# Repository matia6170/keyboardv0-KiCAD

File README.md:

# Keyboard v0 Design
KiCAD9 Schematic/PCB layout of the first keyboard prototype.

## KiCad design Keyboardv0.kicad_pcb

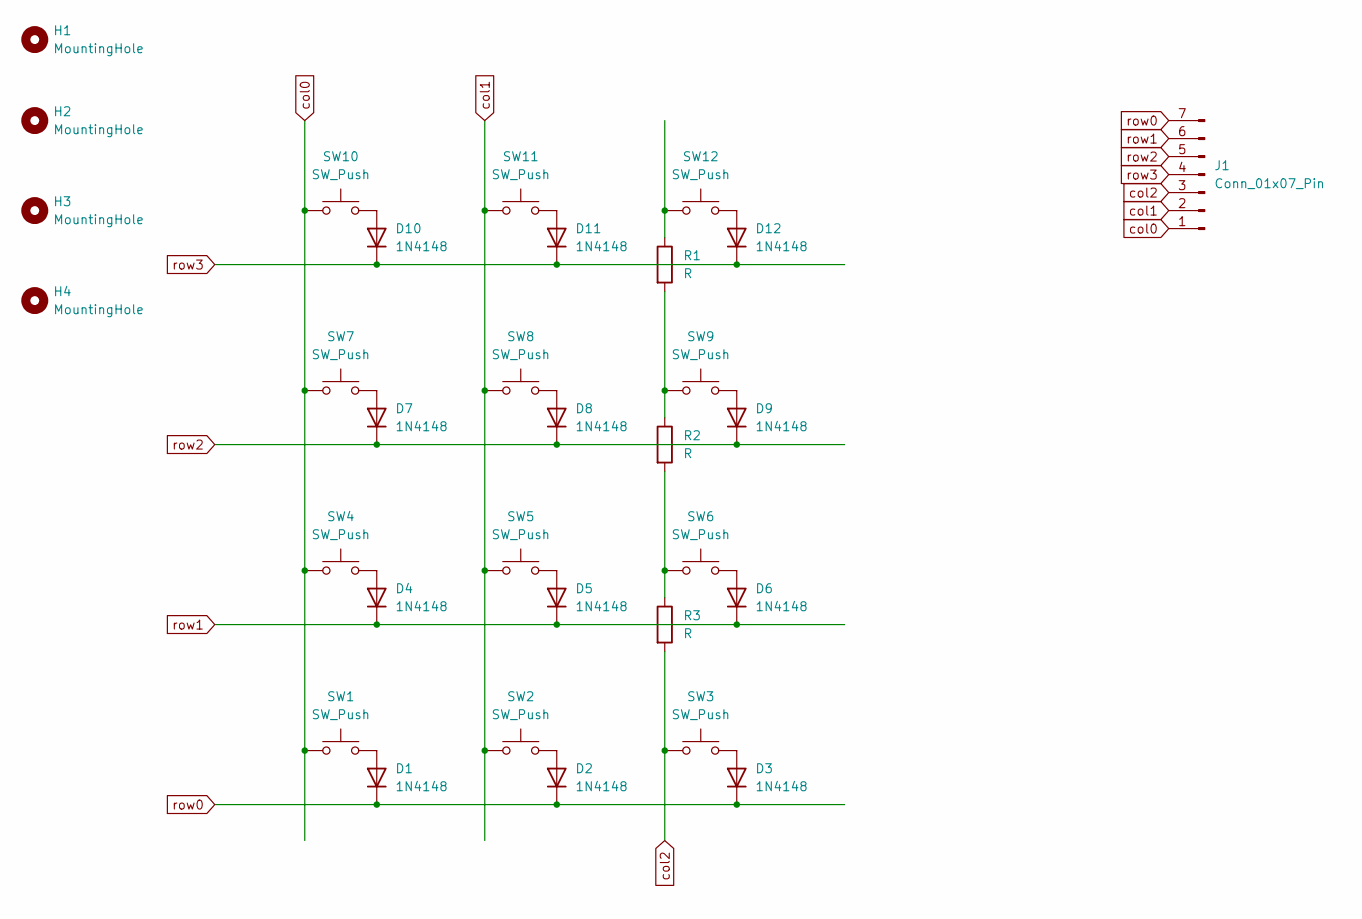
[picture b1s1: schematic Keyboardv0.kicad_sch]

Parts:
D1, D2, D3, D4, D5, D6, D7, D8, D9, D10, D11, D12: 1N4148; D_SOD-123
H1, H2, H3, H4: MountingHole; MountingHole_3.2mm_M3
J1: Conn_01x07_Pin; PinHeader_1x07_P2.54mm_Vertical
R1, R2, R3: R; R_Axial_DIN0204_L3.6mm_D1.6mm_P5.08mm_Horizontal
SW1, SW2, SW3, SW4, SW5, SW6, SW7, SW8, SW9, SW10, SW11, SW12: SW_Push; SW_Cherry_MX_PCB_1.00u

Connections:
unnamed: D1.2 (A), SW1.2
unnamed: D2.2 (A), SW2.2
unnamed: D3.2 (A), SW3.2
unnamed: D4.2 (A), SW4.2
unnamed: D5.2 (A), SW5.2
unnamed: D6.2 (A), SW6.2
unnamed: D7.2 (A), SW7.2
unnamed: D8.2 (A), SW8.2
unnamed: D9.2 (A), SW9.2
unnamed: D10.2 (A), SW10.2
unnamed: D11.2 (A), SW11.2
unnamed: D12.2 (A), SW12.2
unnamed: R1.1, SW12.1
unnamed: R1.2, R2.1, SW9.1
unnamed: R2.2, R3.1, SW6.1
col0: J1.1, SW1.1, SW4.1, SW7.1, SW10.1
col1: J1.2, SW2.1, SW5.1, SW8.1, SW11.1
col2: J1.3, R3.2, SW3.1
row0: D1.1 (K), D2.1 (K), D3.1 (K), J1.7
row1: D4.1 (K), D5.1 (K), D6.1 (K), J1.6
row2: D7.1 (K), D8.1 (K), D9.1 (K), J1.5
row3: D10.1 (K), D11.1 (K), D12.1 (K), J1.4

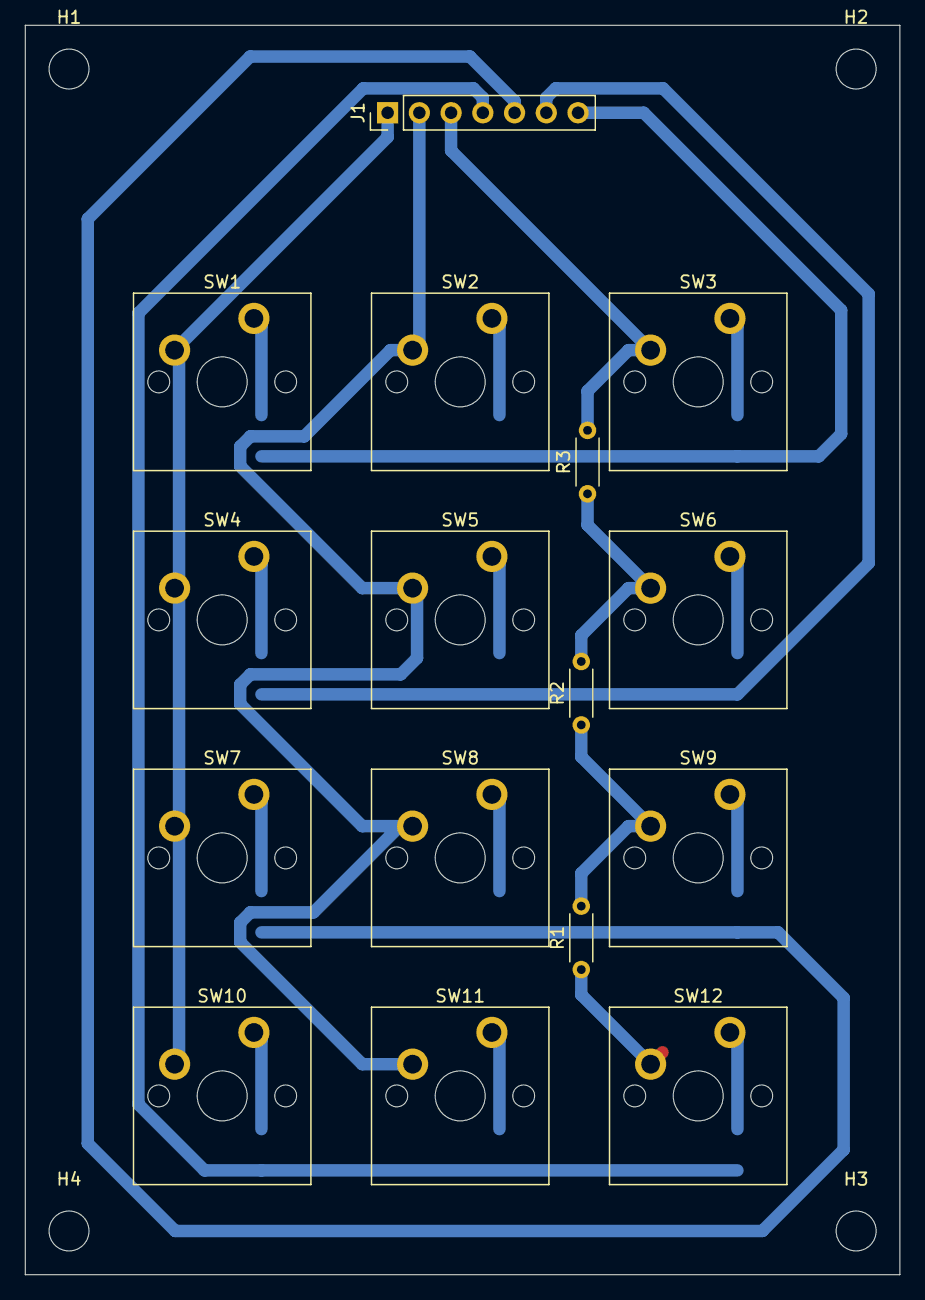
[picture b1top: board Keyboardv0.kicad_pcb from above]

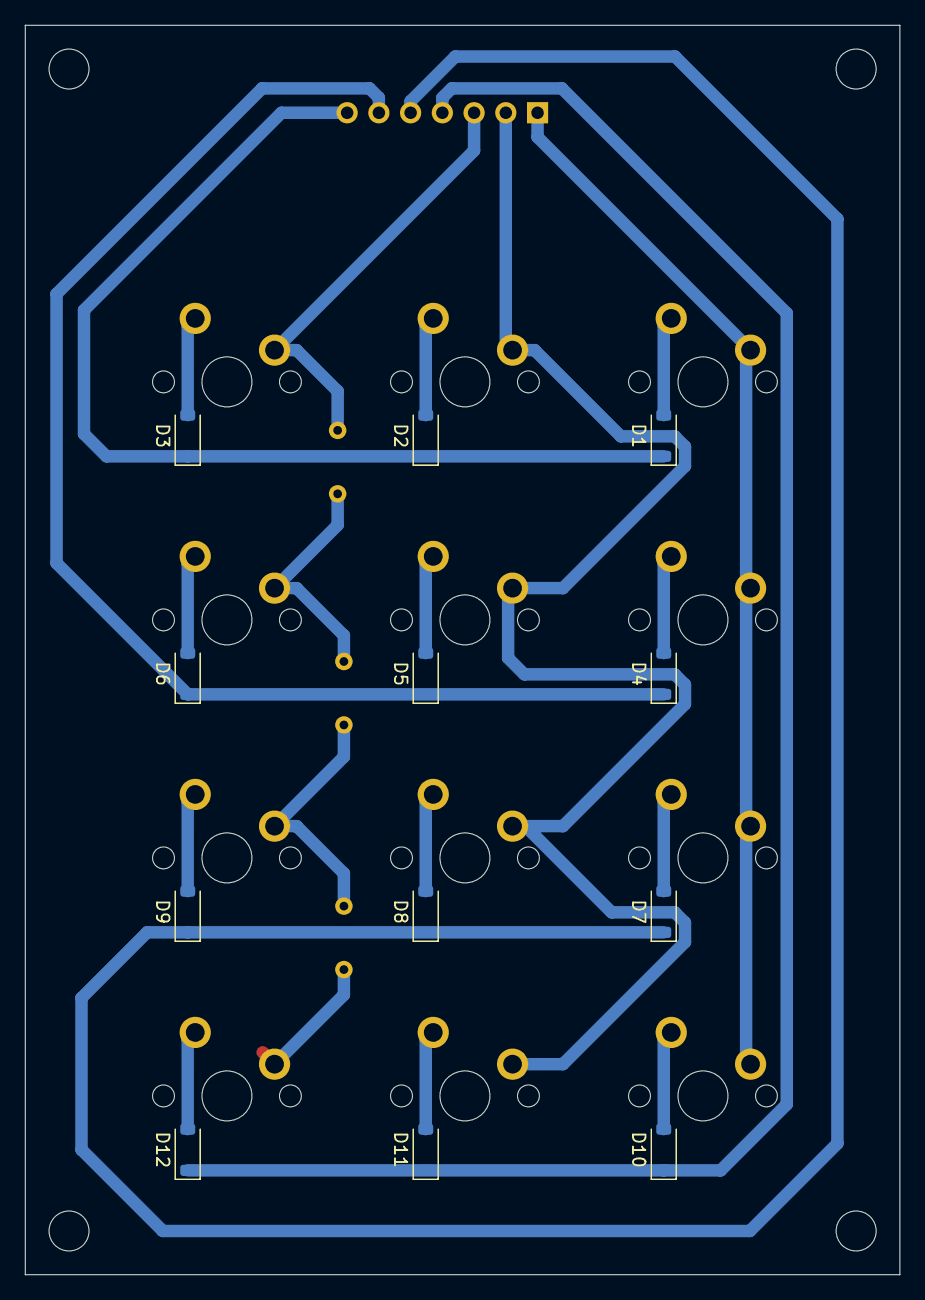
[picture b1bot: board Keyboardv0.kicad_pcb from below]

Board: 2 copper layers, 70.0 x 100.0 mm, 32 parts (12 on the bottom side), 22 nets.

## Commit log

2025-12-13 Completed just the ekeyboard matrix layout with breakout pins. 3x4 layout
2025-12-17 readme
